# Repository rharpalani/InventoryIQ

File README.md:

InventoryIQ
-----
An ESP32 microcontroller-based inventory management solution for the computer engineering lab. Built as a semester-long project for Senior Design (ECE 445) at UIUC. 

Demo Video
-----

Contributors
-----
- Krish Naik Aparaj
- Rohan Harpalani
- Rushil Duggal

Academic Integrity
-----
In accordance with the terms of the accompanying license, the code within this project is available for use. However, all users, particularly those in academic settings, are required to adhere to their respective institutional policies concerning academic integrity. Users are advised to consult their institution's student code of conduct, as well as the section below, to ensure compliance with such policies.

It is the sole responsibility of each user to ascertain that their use of this code conforms to the standards and requirements set forth by their specific course, department, or academic institution. The author of this project expressly disclaims any and all responsibility for any violations of academic integrity that may occur as a result of individuals using, copying, or otherwise engaging with any portion of this code. Users are hereby notified that they bear full responsibility for ensuring that their use of the project's code does not infringe upon the principles and rules of academic honesty as defined by their educational institution.

Please review the University of Illinois Student Code before starting,
particularly all subsections of Article 1, Part 4 Academic Integrity and Procedure [here](http://studentcode.illinois.edu/article1_part4_1-401.html).

**§ 1‑402 Academic Integrity Infractions**

(a).	Cheating. No student shall use or attempt to use in any academic exercise materials, information, study aids, or electronic data that the student knows or should know is unauthorized. Instructors are strongly encouraged to make in advance a clear statement of their policies and procedures concerning the use of shared study aids, examination files, and related materials and forms of assistance. Such advance notification is especially important in the case of take-home examinations. During any examination, students should assume that external assistance (e.g., books, notes, calculators, and communications with others) is prohibited unless specifically authorized by the Instructor. A violation of this section includes but is not limited to:

(1)	Allowing others to conduct research or prepare any work for a student without prior authorization from the Instructor, including using the services of commercial term paper companies. 

(2)	Submitting substantial portions of the same academic work for credit more than once or by more than one student without authorization from the Instructors to whom the work is being submitted. 

(3) Working with another person without authorization to satisfy an individual assignment.

(b) Plagiarism. No student shall represent the words, work, or ideas of another as his or her own in any academic endeavor. A violation of this section includes but is not limited to:

(1)	Copying: Submitting the work of another as one’s own. 

(2)	Direct Quotation: Every direct quotation must be identified by quotation marks or by appropriate indentation and must be promptly cited. Proper citation style for many academic departments is outlined in such manuals as the MLA Handbook or K.L. Turabian’s A Manual for Writers of Term Papers, Theses and Dissertations. These and similar publications are available in the University bookstore or library. The actual source from which cited information was obtained should be acknowledged.

(3)	Paraphrase: Prompt acknowledgment is required when material from another source is paraphrased or summarized in whole or in part. This is true even if the student’s words differ substantially from those of the source. A citation acknowledging only a directly quoted statement does not suffice as an acknowledgment of any preceding or succeeding paraphrased material. 

(4)	Borrowed Facts or Information: Information obtained in one’s reading or research that is not common knowledge must be acknowledged. Examples of common knowledge might include the names of leaders of prominent nations, basic scientific laws, etc. Materials that contribute only to one’s general understanding of the subject may be acknowledged in a bibliography and need not be immediately cited. One citation is usually sufficient to acknowledge indebtedness when a number of connected sentences in the paper draw their special information from one source.

(c) Fabrication. No student shall falsify or invent any information or citation in an academic endeavor. A violation of this section includes but is not limited to:

(1)	Using invented information in any laboratory experiment or other academic endeavor without notice to and authorization from the Instructor or examiner. It would be improper, for example, to analyze one sample in an experiment and covertly invent data based on that single experiment for several more required analyses. 

(2)	Altering the answers given for an exam after the examination has been graded. 

(3)	Providing false or misleading information for the purpose of gaining an academic advantage.

(d)	Facilitating Infractions of Academic Integrity. No student shall help or attempt to help another to commit an infraction of academic integrity, where one knows or should know that through one’s acts or omissions such an infraction may be facilitated. A violation of this section includes but is not limited to:

(1)	Allowing another to copy from one’s work. 

(2)	Taking an exam by proxy for someone else. This is an infraction of academic integrity on the part of both the student enrolled in the course and the proxy or substitute. 

(3)	Removing an examination or quiz from a classroom, faculty office, or other facility without authorization.

(e)	Bribes, Favors, and Threats. No student shall bribe or attempt to bribe, promise favors to or make threats against any person with the intent to affect a record of a grade or evaluation of academic performance. This includes conspiracy with another person who then takes the action on behalf of the student.

(f)	Academic Interference. No student shall tamper with, alter, circumvent, or destroy any educational material or resource in a manner that deprives any other student of fair access or reasonable use of that material or resource. 

(1)	Educational resources include but are not limited to computer facilities, electronic data, required/reserved readings, reference works, or other library materials. 

(2)	Academic interference also includes acts in which the student committing the infraction personally benefits from the interference, regardless of the effect on other students.

LEGAL
-----
Permission to use, copy, modify, and distribute this software and its
documentation for any purpose, without fee, and without written agreement is
hereby granted, provided that the above copyright notice and the following
two paragraphs appear in all copies of this software.

IN NO EVENT SHALL THE AUTHOR OR THE UNIVERSITY OF ILLINOIS BE LIABLE TO
ANY PARTY FOR DIRECT, INDIRECT, SPECIAL, INCIDENTAL, OR CONSEQUENTIAL
DAMAGES ARISING OUT  OF THE USE OF THIS SOFTWARE AND ITS DOCUMENTATION,
EVEN IF THE AUTHOR AND/OR THE UNIVERSITY OF ILLINOIS HAS BEEN ADVISED
OF THE POSSIBILITY OF SUCH DAMAGE.

THE AUTHOR AND THE UNIVERSITY OF ILLINOIS SPECIFICALLY DISCLAIM ANY
WARRANTIES, INCLUDING, BUT NOT LIMITED TO, THE IMPLIED WARRANTIES OF
MERCHANTABILITY AND FITNESS FOR A PARTICULAR PURPOSE.  THE SOFTWARE

PROVIDED HEREUNDER IS ON AN "AS IS" BASIS, AND NEITHER THE AUTHOR NOR
THE UNIVERSITY OF ILLINOIS HAS ANY OBLIGATION TO PROVIDE MAINTENANCE,
SUPPORT, UPDATES, ENHANCEMENTS, OR MODIFICATIONS."

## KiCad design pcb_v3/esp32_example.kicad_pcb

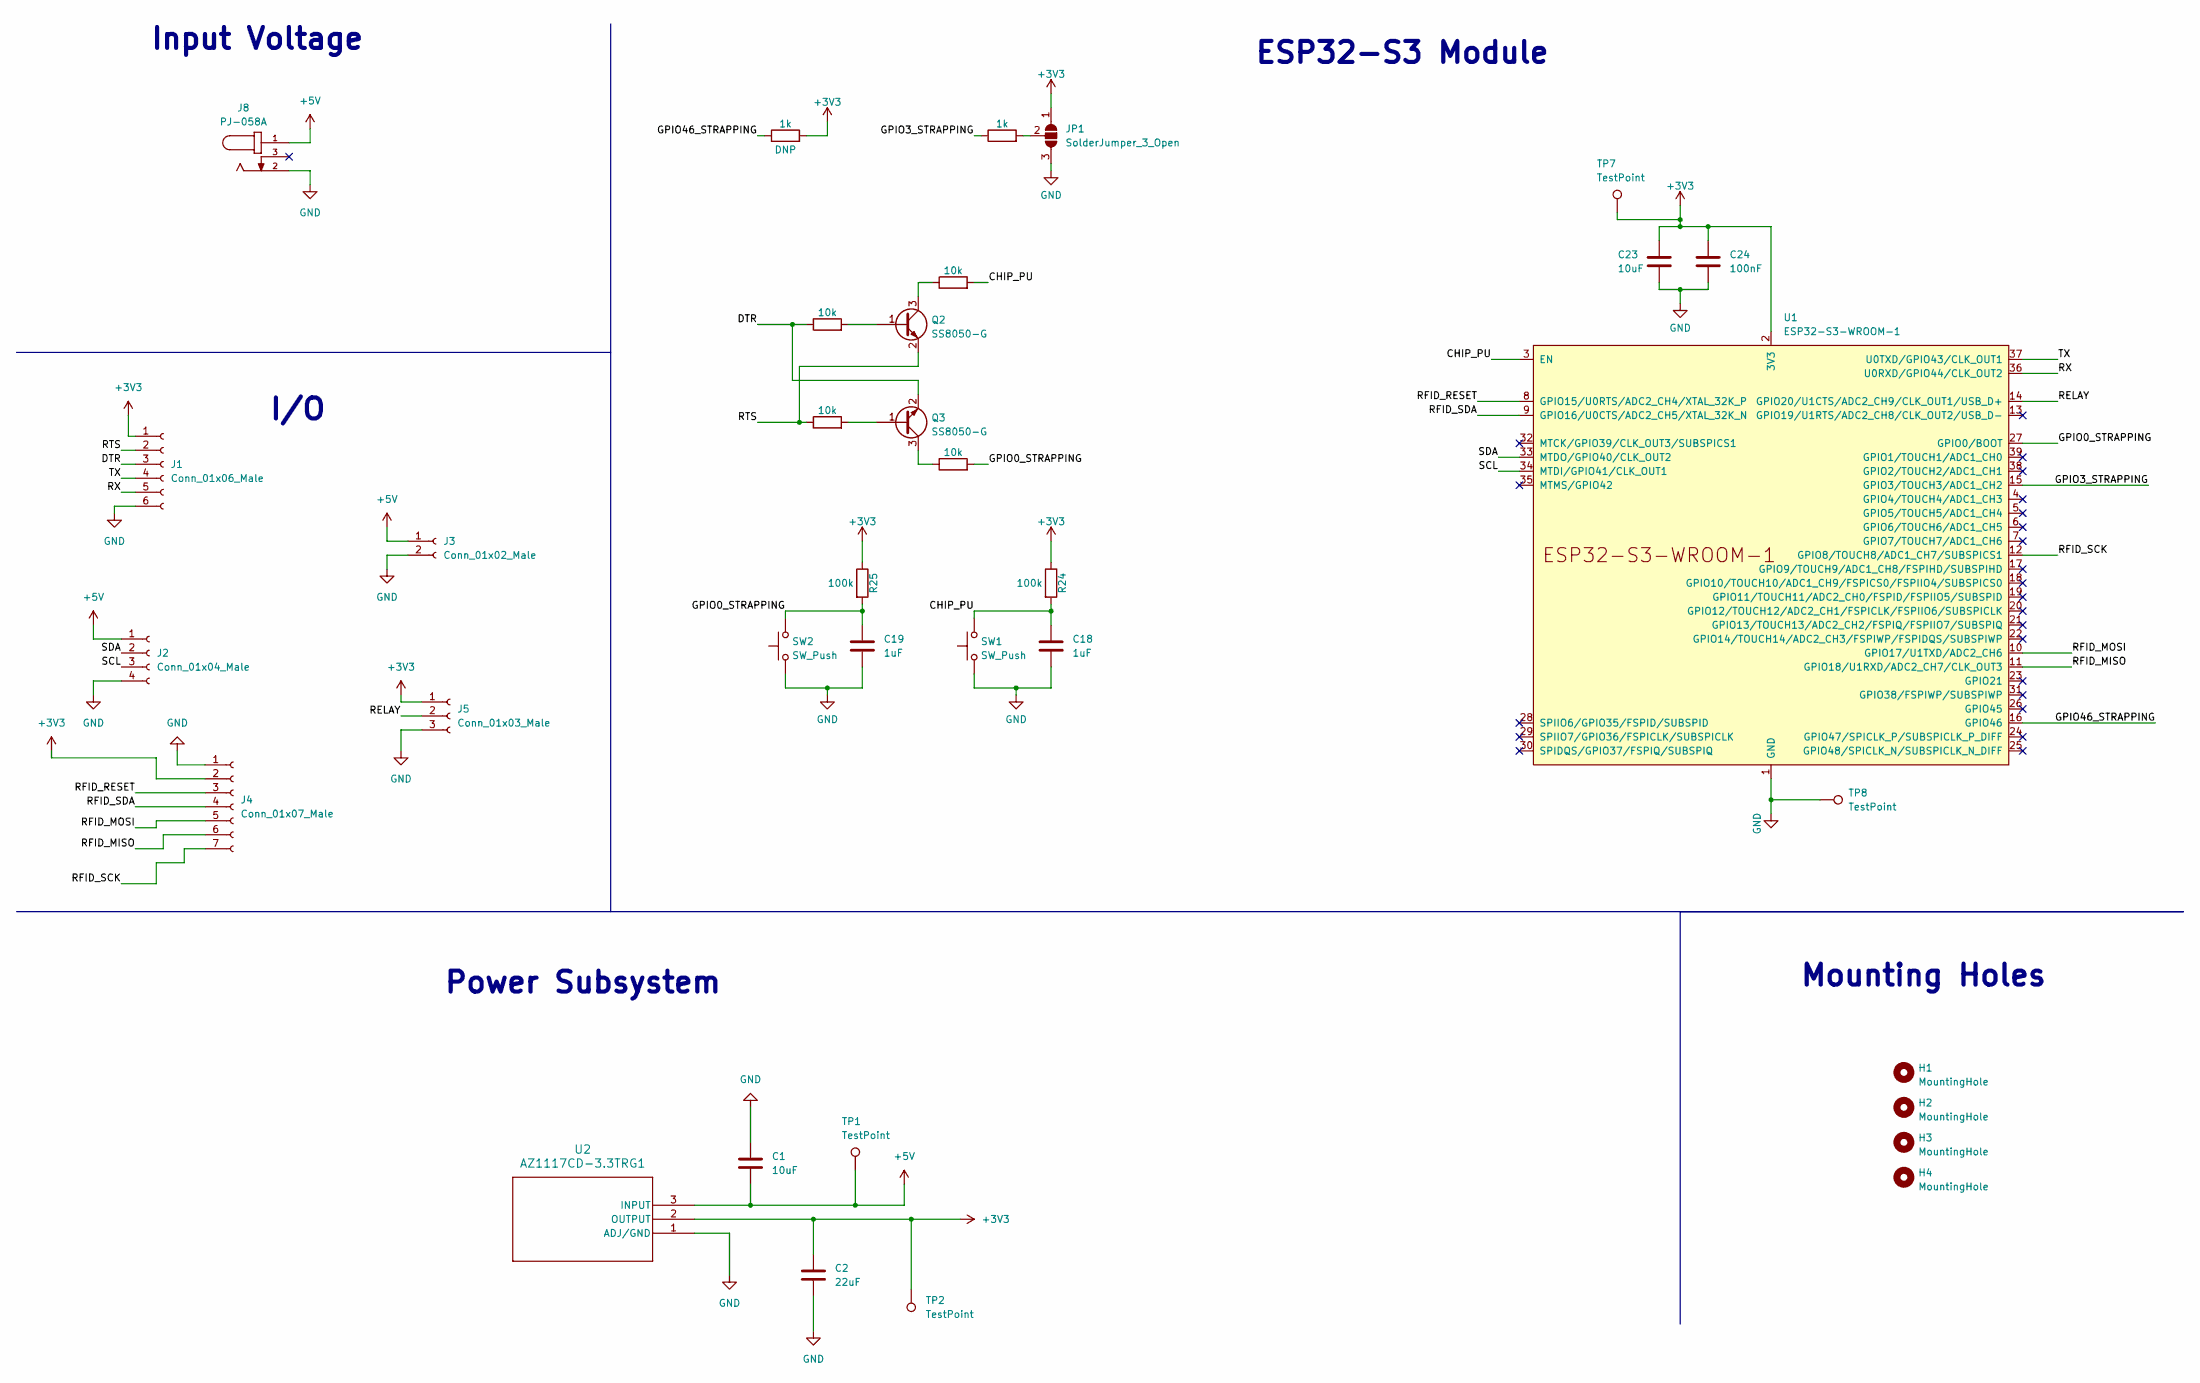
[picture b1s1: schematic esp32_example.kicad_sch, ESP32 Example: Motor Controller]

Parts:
C1, C23: 10uF; G-31_MUR
C2: 22uF; CAP_GRM18ME15D_1P6XP8_MUR
C18, C19: 1uF; G-155_MUR
C24: 100nF; CAP_CL10_SAM
H1, H2, H3, H4: MountingHole; MountingHole_3.2mm_M3
J1: Conn_01x06_Male; Molex_KK-254_AE-6410-06A_1x06_P2.54mm_Vertical
J2: Conn_01x04_Male; Molex_KK-254_AE-6410-04A_1x04_P2.54mm_Vertical
J3: Conn_01x02_Male; Molex_KK-254_AE-6410-02A_1x02_P2.54mm_Vertical
J4: Conn_01x07_Male; Molex_KK-254_AE-6410-07A_1x07_P2.54mm_Vertical
J5: Conn_01x03_Male; Molex_KK-254_AE-6410-03A_1x03_P2.54mm_Vertical
J8: PJ-058A; CUI_PJ-058A; PARTREV 1.02
JP1: SolderJumper_3_Open; SolderJumper-3_P2.0mm_Open_TrianglePad1.0x1.5mm
Q2, Q3: SS8050-G; SOT-23
R12, R17: 1k; RES_ERJPA3J102V
R13, R14, R18, R19: 10k; RC0805N_PAN
R24, R25: 100k; RESC3116X65N
SW1, SW2: SW_Push; SW_SPST_B3S-1000
TP1, TP2, TP7, TP8: TestPoint; TestPoint_Pad_D2.0mm
U1: ESP32-S3-WROOM-1
U2: AZ1117CD-3.3TRG1; TO252-2-3.3V_DIO

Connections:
+3V3: C2.1, C23.1, C24.1, J1.1, J4.2, J5.1, JP1.1 (A), R12.2, R24.1, R25.1, TP2.1, TP7.1, U1.2 (3V3), U2.2 (OUTPUT)
+5V: C1.2, J2.1, J3.1, J8.1, TP1.1, U2.3 (INPUT)
/CHIP_PU: C18.1, R18.2, R24.2, SW1.2, U1.3 (EN)
/DTR: J1.3, Q3.2 (E), R13.1
/GPIO0_STRAPPING: C19.1, R19.2, R25.2, SW2.2, U1.27 (GPIO0/BOOT)
/GPIO3_STRAPPING: R17.1, U1.15 (GPIO3/TOUCH3/ADC1_CH2)
/GPIO46_STRAPPING: R12.1, U1.16 (GPIO46)
/RELAY: J5.2, U1.14 (GPIO20/U1CTS/ADC2_CH9/CLK_OUT1/USB_D+)
/RFID_MISO: J4.6, U1.11 (GPIO18/U1RXD/ADC2_CH7/CLK_OUT3)
/RFID_MOSI: J4.5, U1.10 (GPIO17/U1TXD/ADC2_CH6)
/RFID_RESET: J4.3, U1.8 (GPIO15/U0RTS/ADC2_CH4/XTAL_32K_P)
/RFID_SCK: J4.7, U1.12 (GPIO8/TOUCH8/ADC1_CH7/SUBSPICS1)
/RFID_SDA: J4.4, U1.9 (GPIO16/U0CTS/ADC2_CH5/XTAL_32K_N)
/RTS: J1.2, Q2.2 (E), R14.1
/RX: J1.5, U1.36 (U0RXD/GPIO44/CLK_OUT2)
/SCL: J2.3, U1.34 (MTDI/GPIO41/CLK_OUT1)
/SDA: J2.2, U1.33 (MTDO/GPIO40/CLK_OUT2)
/TX: J1.4, U1.37 (U0TXD/GPIO43/CLK_OUT1)
GND: C1.1, C2.2, C18.2, C19.2, C23.2, C24.2, J1.6, J2.4, J3.2, J4.1, J5.3, J8.2, JP1.3 (B), SW1.1, SW2.1, TP8.1, U1.1 (GND), U1.40 (GND), U1.41 (GND), U2.1 (ADJ/GND)
unnamed: JP1.2 (C), R17.2
unnamed: Q2.1 (B), R13.2
unnamed: Q2.3 (C), R18.1
unnamed: Q3.1 (B), R14.2
unnamed: Q3.3 (C), R19.1

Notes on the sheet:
Power Subsystem
ESP32-S3 Module
Mounting Holes
I/O
Input Voltage

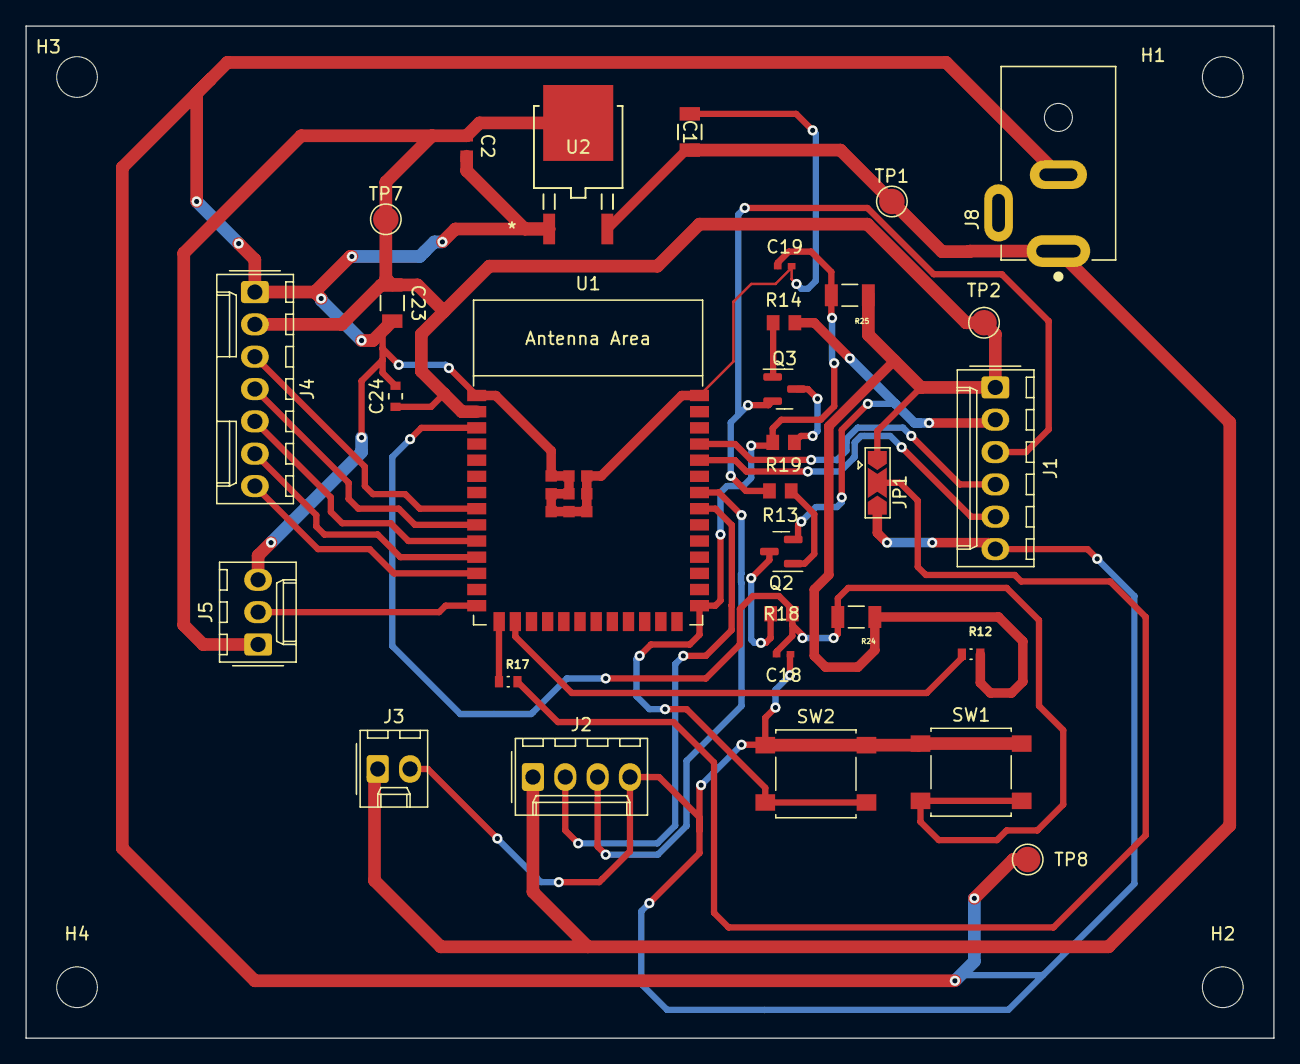
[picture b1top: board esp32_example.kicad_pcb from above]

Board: 2 copper layers, 98.0 x 79.5 mm, 35 parts (0 on the bottom side), 24 nets.

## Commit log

2023-09-12 setting up digital notebook
2023-10-08 Worklog for 9/25 week
2023-11-15 software working
2023-12-04 initializing
2023-12-04 Delete rohan_esp32 directory
    fixing
2023-12-04 Delete firestore.py
    fixing
2023-12-04 fixing
2023-12-04 testing pics
2023-12-04 committing
2023-12-04 updating journal
2023-12-07 transferring journal entries
2023-12-07 transferring lab entries
2023-12-07 adding report
2023-12-07 QR Identification Code
2023-12-08 Final Push
2024-03-15 editing readme
